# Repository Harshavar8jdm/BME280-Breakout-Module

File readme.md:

# BME280 Environmental Sensor Breakout Module

An ultra-compact ($12 \times 10\,\text{mm}$) hardware breakout board for the **Bosch BME280** humidity, pressure, and temperature sensor. Designed in KiCad, this board breaks out the essential I2C signals to a standard $2.54\,\text{mm}$ header for seamless integration into low-power embedded systems and microcontroller prototyping.

## 3D Board Renders

| Top View | Bottom View |
| :---: | :---: |
|  |  |

---

## Technical Specifications

| Parameter | Value / Description |
| :--- | :--- |
| **Dimensions** | $12\,\text{mm} \times 10\,\text{mm}$ |
| **Supply Voltage ($V_{DD}$ / $V_{DDIO}$)** | $3.3\,\text{V}$ DC |
| **Communication Interface** | I2C (Hardwired) |
| **I2C Slave Address** | `0x77` (`SDO` pulled HIGH to $V_{DDIO}$) |
| **I2C Pull-Up Resistors** | $2.2\,\text{k}\Omega$ (Supports Standard & Fast Mode) |
| **Header Pitch** | $2.54\,\text{mm}$ ($100\,\text{mil}$) |
| **Passives Form Factor** | 0603 (1608 Metric) |
| **EDA Software** | KiCad EDA v10.0.4 |

---

## Pinout Configuration

The module features a 4-pin header interface designed for easy breadboard or jumper cable hookup:

| Header Pin | Label | Type | Schematic Net | Description |
| :---: | :--- | :--- | :--- | :--- |
| **1** | `3.3V` | Power | `+3.3V` | Main Power Supply ($3.3\,\text{V}$) |
| **2** | `SCK` | Input | `SCK` / `SCL` | I2C Serial Clock line |
| **3** | `GND` | Power | `GND` | System Ground Reference |
| **4** | `SDA` | I/O | `SDA` | I2C Serial Data line |

> **Note on Crosstalk:** Placing Ground (`GND`) between `SCK` and `SDA` on the physical pin header provides physical shielding against signal crosstalk across external cables.

---

## Schematic & Hardware Design

### Design Choices
* **Hardwired I2C Mode:** Pin 2 (`CSB`) is connected directly to $V_{DDIO}$ ($+3.3\,\text{V}$), permanently selecting the I2C interface protocol and disabling SPI.
* **Slave Address Selection:** Pin 5 (`SDO`) is tied to $V_{DDIO}$, setting the default 7-bit I2C address to **`0x77`**.
* **Bus Termination:** $2.2\,\text{k}\Omega$ pull-up resistors ($R_1, R_2$) are included on both `SDA` and `SCK` lines to guarantee fast rise times ($t_r < 300\,\text{ns}$) for 400 kHz Fast-Mode I2C operation.
* **Power Supply Decoupling:** Dedicated $100\,\text{nF}$ ceramic decoupling capacitors ($C_1, C_2$) are placed close to the $V_{DD}$ and $V_{DDIO}$ power pins to filter high-frequency noise and voltage ripple.

---

## PCB Layout

| Top Layer (F.Cu) | Bottom Layer (B.Cu) | Combined Stackup |
| :---: | :---: | :---: |
|  |  |  |

---

                                    # Project Documentation

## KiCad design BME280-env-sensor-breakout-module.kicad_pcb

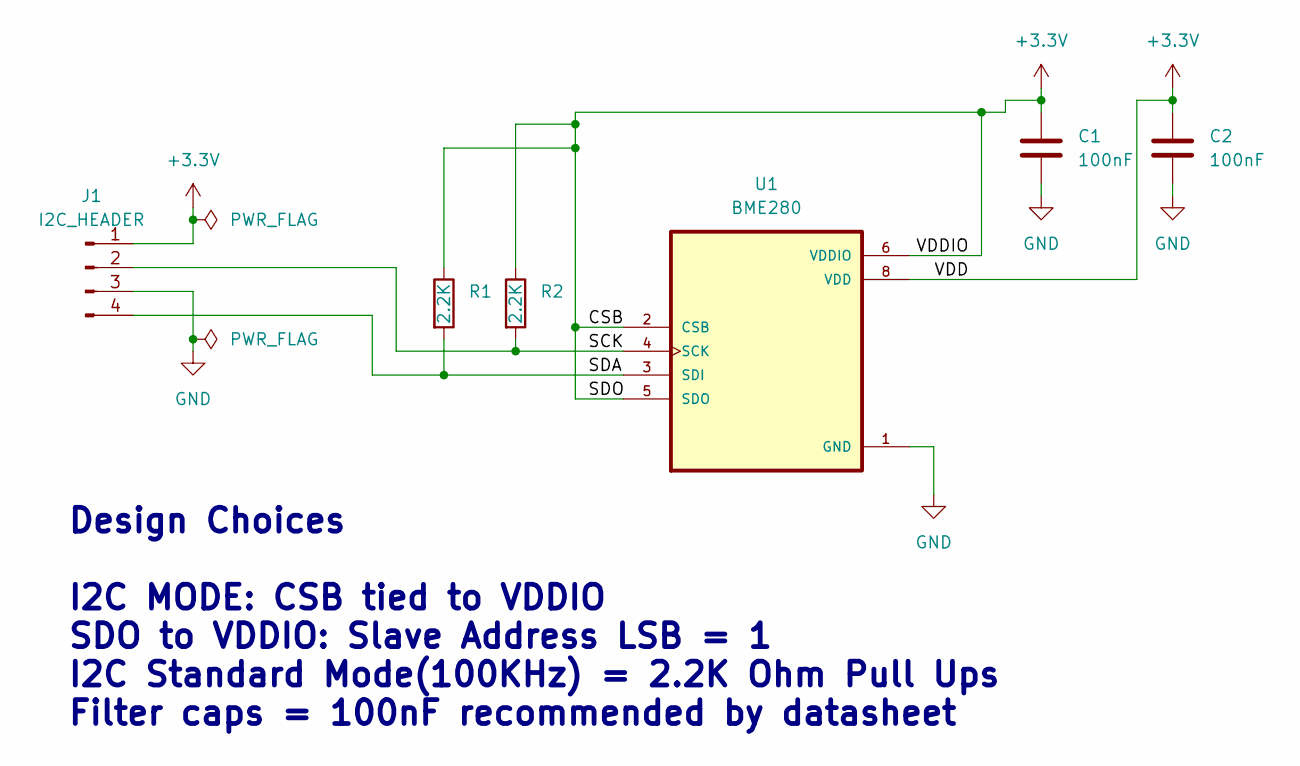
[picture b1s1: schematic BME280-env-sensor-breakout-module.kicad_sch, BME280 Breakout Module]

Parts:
C1, C2: 100nF; C_0603_1608Metric_Pad1.08x0.95mm_HandSolder
J1: I2C_HEADER; PinHeader_1x04_P2.54mm_Vertical
R1, R2: 2.2K; R_0603_1608Metric_Pad0.98x0.95mm_HandSolder
U1: BME280; PSON65P250X250X100-8N

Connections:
+3.3V: C1.1, C2.1, J1.1, R1.1, R2.1, U1.2 (CSB), U1.5 (SDO), U1.6 (VDDIO), U1.8 (VDD)
/SCK: J1.2, R2.2, U1.4 (SCK)
/SDA: J1.4, R1.2, U1.3 (SDI)
GND: C1.2, C2.2, J1.3, U1.1 (GND), U1.7 (GND)

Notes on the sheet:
Design Choices I2C MODE: CSB tied to VDDIO SDO to VDDIO: Slave Address LSB = 1 I2C Standard Mode(100KHz) = 2.2K Ohm Pull Ups Filter caps = 100nF recommended by datasheet

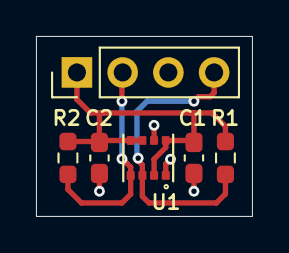
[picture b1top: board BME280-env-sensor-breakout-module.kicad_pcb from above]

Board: 2 copper layers, 12.0 x 10.0 mm, 6 parts (0 on the bottom side), 4 nets.
